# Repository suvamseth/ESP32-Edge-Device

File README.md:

<div align="center">

# Industrial IoT Smart Edge Device 

**A robust, hybrid sensing Smart Edge Device designed for  home energy monitoring, industrial-grade energy monitoring and protection. Features dual-protocol communication (MQTT & Modbus).**

-blue)

</div>
---

## 📖 Overview
This Smart Edge Node (SED) functions as a comprehensive data acquisition and protection unit for household and industrial loads. Unlike standard smart plugs, this device integrates **hybrid sensing** architecture: it uses a **PZEM-004T** for precision metering and features **AMC1200 Isolation Amplifier** used for galvanic isolation and transient analysis, it also executes the on/off command of load using relay.

The system is engineered to prioritize reliability in noisy electrical environments by utilizing **W5500 Ethernet** for hardwired communication, supporting both **MQTT** for cloud-server dashboards (Node-RED) and **Modbus TCP** for legacy industrial integration.

---

## 📸 Visuals
| **3D PCB Render** | **Real Device** |
|:---:|:---:|
|  |  |
| *Final PCB Design (KiCad)* | *Final PCB from the fabricator* |

> *Note: See the `/schematics` folder for the full PDF circuit diagram.*

---

## ⚡ Key Features

### 1. Hybrid Sensing Architecture
* **Precision Metering (PZEM-004T):**
    * Accurate calculation of RMS Voltage, Current, Active Power, Energy (kWh), Frequency, and Power Factor.
    * Sends this data to esp32 using UART protocol.
* **Transient Protection (AMC1200):**
    * Provides **4250V peak galvanic isolation**.
    * Feeds a high-speed analog signal to the ESP32 to detect **Voltage Surges and Dips** in real-time (sub-cycle detection), triggering safety cutoffs faster than digital sensors allow.

### 2. Industrial Connectivity
* **Ethernet (W5500):** Uses SPI interface for stable, low-latency connection, eliminating Wi-Fi instability in industrial settings.
* **Dual-Protocol Stack:**
    * **MQTT:** Publishes telemetry to a local broker for visualization on Node-RED.
    * **Modbus TCP:** Acts as a slave device, allowing PLCs or SCADA systems to poll data.

### 3. Load Control & Safety
* **30A Relay Integration:** Allows remote ON/OFF control via dashboard or automated safety disconnection during surge events.
* **Isolated Logic:** Low-voltage logic (ESP32) is completely isolated from High-Voltage mains via the AMC1200 and PC817 Optocouplers.

---
## 📊 Dashboard View
**
*Real-time monitoring interface showing energy consumption metrics and relay status.*

---
## 👨‍💻 Author
**Suvam Seth**
*Power Engineering Student | PCB Design | IoT Systems*

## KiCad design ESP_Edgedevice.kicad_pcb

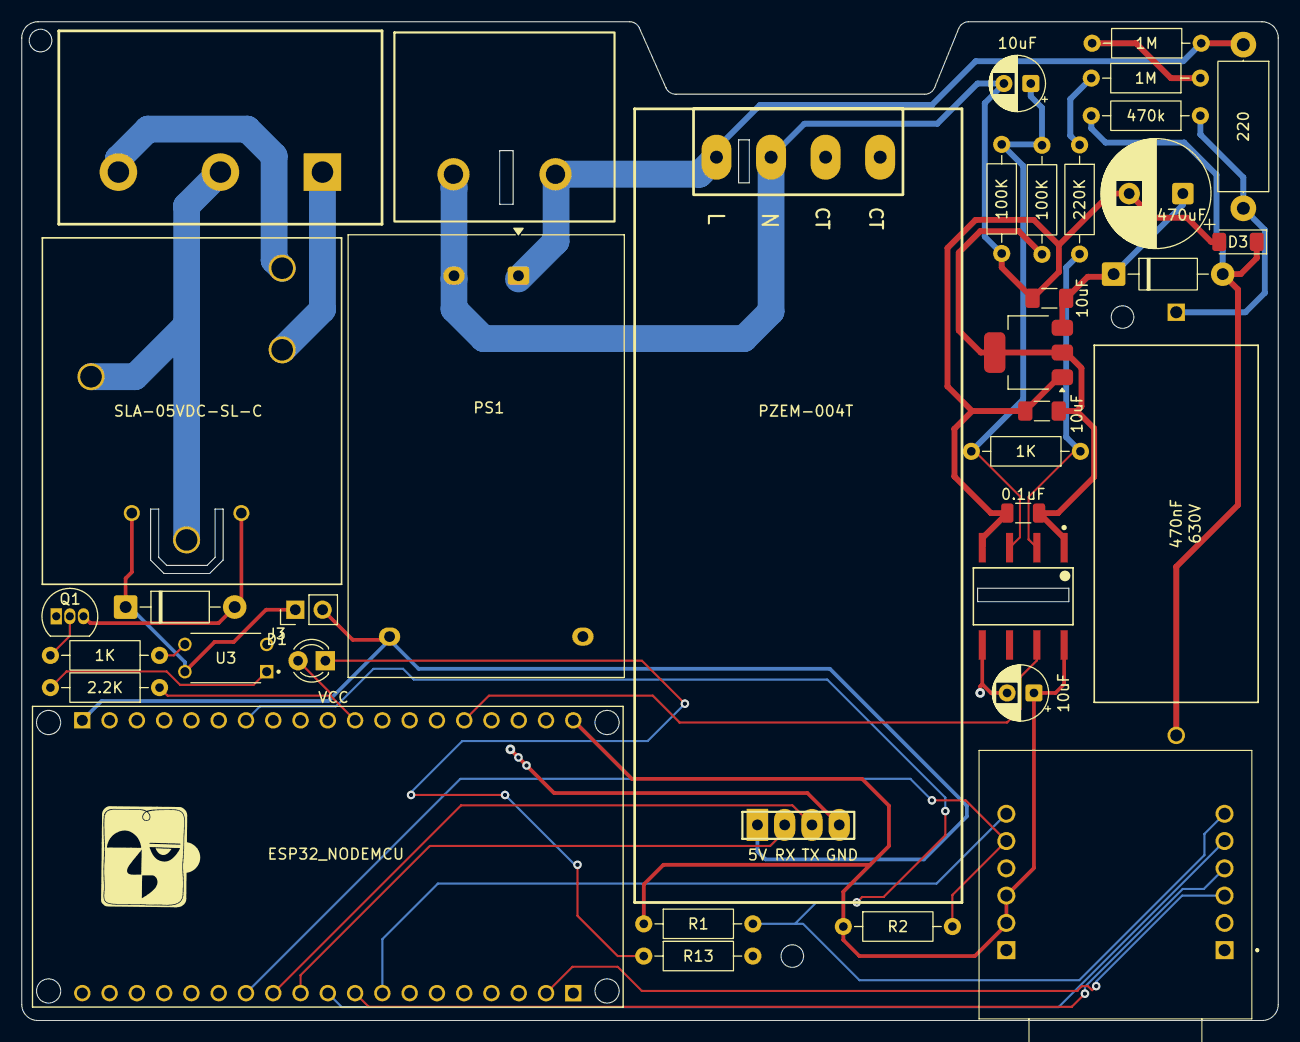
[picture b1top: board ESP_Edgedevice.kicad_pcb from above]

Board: 2 copper layers, 117.0 x 93.0 mm, 39 parts (0 on the bottom side), 32 nets.

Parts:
C1: 470nF; CAP_150AXIAL_RF_CND
C2: 470uF; CP_Radial_D10.0mm_P5.00mm
C3, C4: 10uF; C_1206_3216Metric_Pad1.33x1.80mm_HandSolder
C5, C7: 10uF; CP_Radial_D5.0mm_P2.50mm
C6: 0.1uF; C_1206_3216Metric
D1: LED; LED_D3.0mm
D2, D4: 1N4007; D_DO-41_SOD81_P10.16mm_Horizontal
D3: 7.5; D_MiniMELF
H1: WIZ850IO
H2, H3, H5: MountingHole; MountingHole_2.1mm
J1: HB9500-9.5-3P; CONN-TH_HB9500-9.5-3P
J2: Barrier Terminal; Terminal_Block_9.5mm-2
J3: Conn_01x02_Pin; PinHeader_1x02_P2.54mm_Vertical
K1: SLA-05VDC-SL-C; K_SLA_C_NFR
PS1: HLK-5M05; Converter_ACDC_Hi-Link_HLK-5Mxx
Q1: S8050; TO-92_Inline
R1, R2: 10K; R_Axial_DIN0207_L6.3mm_D2.5mm_P10.16mm_Horizontal
R3: 2.2K; R_Axial_DIN0207_L6.3mm_D2.5mm_P10.16mm_Horizontal
R4, R12, R13: 1K; R_Axial_DIN0207_L6.3mm_D2.5mm_P10.16mm_Horizontal
R5: 220; R_Axial_DIN0414_L11.9mm_D4.5mm_P15.24mm_Horizontal
R6: 470k; R_Axial_DIN0207_L6.3mm_D2.5mm_P10.16mm_Horizontal
R7, R8: 1M; R_Axial_DIN0207_L6.3mm_D2.5mm_P10.16mm_Horizontal
R9, R10: 100K; R_Axial_DIN0207_L6.3mm_D2.5mm_P10.16mm_Horizontal
R11: 220K; R_Axial_DIN0207_L6.3mm_D2.5mm_P10.16mm_Horizontal
U1: ESP32_NODEMCU; MODULE_ESP32_NODEMCU
U2: PZEM-004T; PZEM-004T V3
U3: PC817X3NSZ1B; DIP762W50P254L495H455Q4
U4: AMS1117-5.0; SOT-223-3_TabPin2
U5: AMC1200SDUBR; DUB0008A-IPC_A

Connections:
/CS: H1.5 (SCNN), U1.J4_10 (G5)
/INT: H1.6 (INTN), R1.2, U1.J5_7 (G12)
/MISO: H1.12 (MISO), U1.J4_8 (G19)
/MOSI: H1.3 (MOSI), U1.J4_2 (G23)
/RESET: H1.11 (RSTN), R2.2, U1.J4_13 (G4)
/RX: U1.J4_11 (G17), U2.3 (RX)
/Relay/Jd_VCC: D2.1 (K), J3.1, K1.1, U3.4
/Relay/Relay: D2.2 (A), K1.2, Q1.3 (C)
/SCK: H1.4 (SCLK), U1.J4_9 (G18)
/TX: U1.J4_12 (G16), U2.2 (TX)
/Voltage Sensing/VDD1: C4.1, C6.2, R9.1, U4.2 (VO), U5.1 (VDD1)
AC sensing: U1.J5_15 (G34), U5.7 (VOUTP)
COM: J1.2, K1.3, K1.4
GND: C7.2, H1.1 (GND_1), H1.2 (GND_2), H1.7 (GND_3), PS1.3 (-Vout), Q1.1 (E), R13.2, U1.J4_1 (GND_1), U1.J4_7 (GND_7), U1.J5_6 (GND_6), U2.1 (GND), U3.2, U5.5 (GND2)
INPUT: D1.2 (A), R3.1, U1.J5_11 (G25)
LIVE: J2.2, PS1.1 (AC/L), R5.1, R7.1, U2.8 (AC-L)
NC: J1.3, K1.6
NEUTRAL: C2.2, C3.2, C4.2, C5.2, C6.1, D3.2 (A), J2.1, PS1.2 (AC/N), R10.2, U2.7 (AC-N), U4.1 (GND), U5.4 (GND1)
NO: J1.1, K1.5
unnamed: C1.1, R5.2, R6.1
unnamed: D1.1 (K), R13.1
unnamed: C1.2, D3.1 (K), D4.2 (A), R6.2
unnamed: C2.1, C3.1, D4.1 (K), U4.3 (VI)
unnamed: Q1.2 (B), R4.2
unnamed: R3.2, U3.1
unnamed: R4.1, U3.3
unnamed: R7.2, R8.1
unnamed: R8.2, R11.1
unnamed: C5.1, R9.2, R10.1, R12.2, U5.3 (VINN)
unnamed: R11.2, R12.1, U5.2 (VINP)
VCC: J3.2, PS1.4 (+Vout), U1.J5_1 (5V), U2.4 (VCC)
VCC_3.3: C7.1, H1.8 (3.3V_1), H1.9 (3.3V_2), R1.1, R2.1, U1.J5_19 (3V3), U5.8 (VDD2)

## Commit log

2025-08-03 Start
2025-08-04 Schematic Of Relay Portion Completed
2025-08-04 30Amp Relay Schematic Completed
2025-08-05 Amc1200 Based Voltage Sensing Schematic Completed
2025-08-05 minor changes
2025-08-06 Final Schematic Editing Completed
2025-08-07 done
2025-08-07 modification
2025-08-07 Schematic Editing Done
2025-08-07 Assignment Of Footprint Done
2025-08-09 Placement Of Component on PCB Done
2025-08-10 PCB Routing Completed
2025-08-15 FINAL COMMIT
2025-11-29 Fix: Corrected Schematic and Updated PCB Layout
2025-11-29 Final Schematic with minor fixes
2025-11-29 Documentation Update For The SED
2025-12-01 Fix: Documentation
2025-12-01 Fix: Readme Updated
2025-12-01 test comit
2025-12-01 pcb layout completed
